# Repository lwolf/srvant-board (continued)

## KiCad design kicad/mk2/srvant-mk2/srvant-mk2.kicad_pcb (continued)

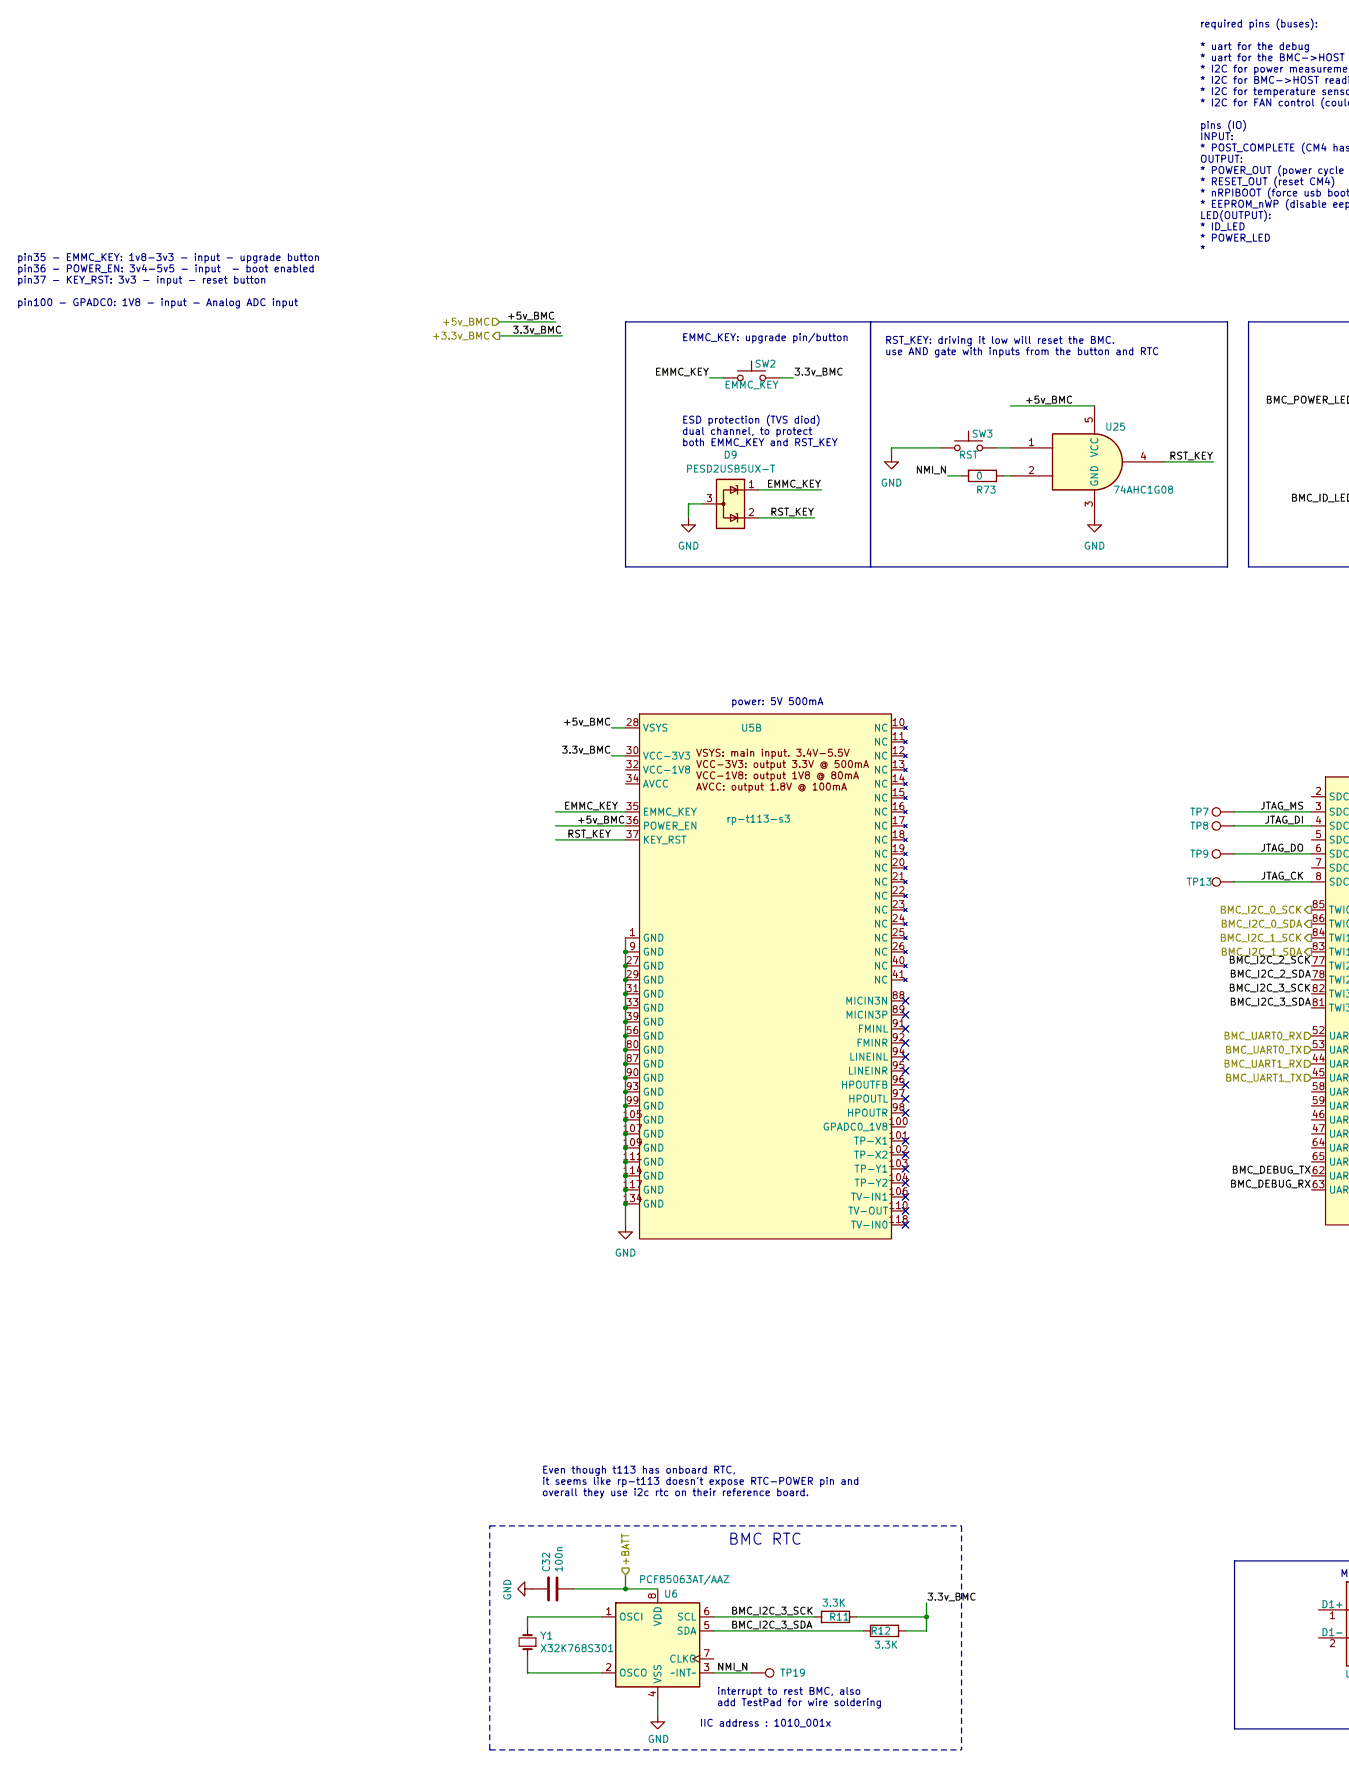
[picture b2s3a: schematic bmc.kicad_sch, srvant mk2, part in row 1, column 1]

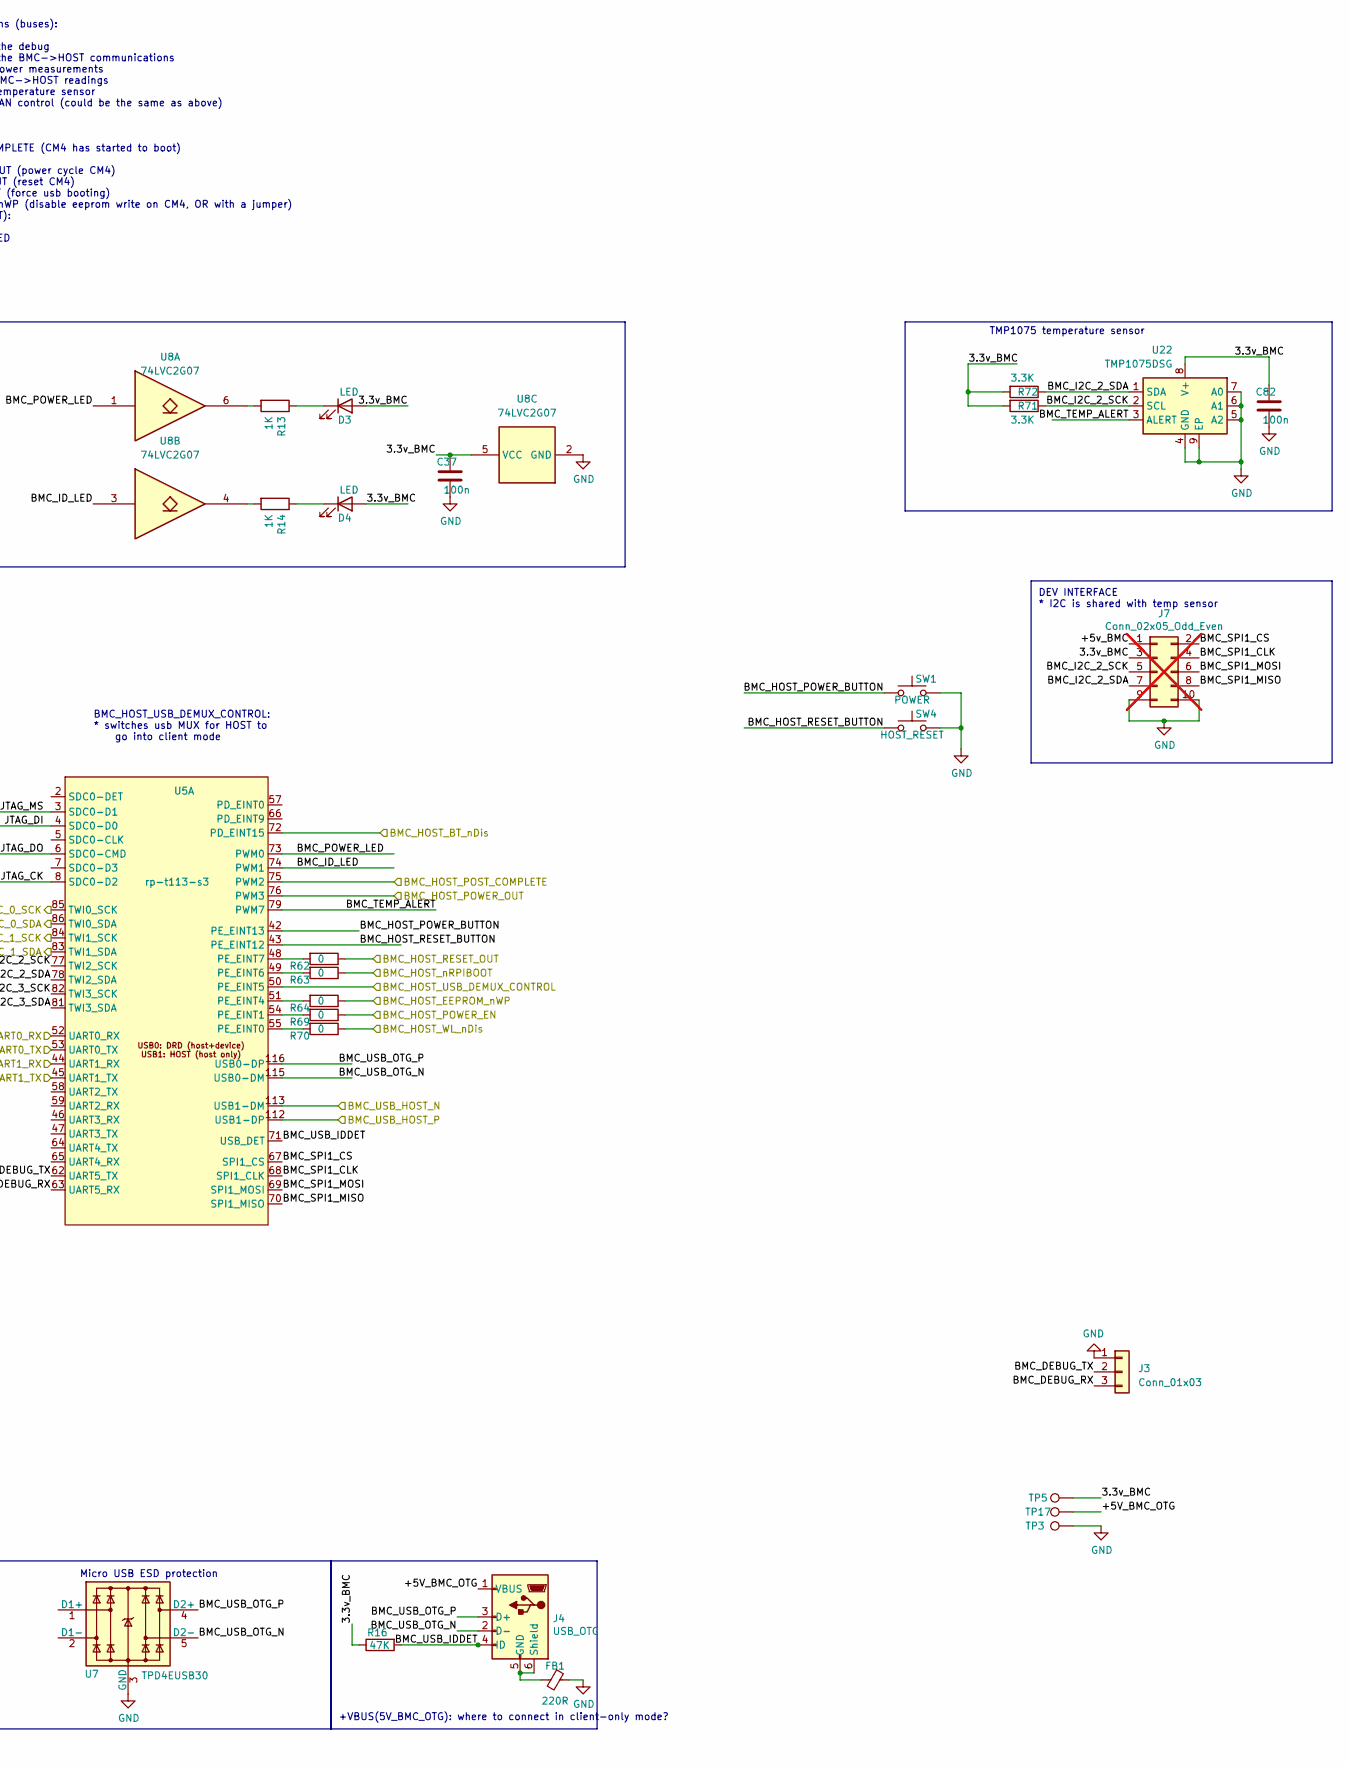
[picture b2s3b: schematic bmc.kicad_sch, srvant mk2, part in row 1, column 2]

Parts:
C32: 100n; C_0402_1005Metric; Part Description 0.1uF 10% 16V Ceramic Capacitor X7R 040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
C37, C82: 100n; C_0402_1005Metric; Part Description 0.1uF 10% 16V Ceramic Capacitor X7R 040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; digikey# EMK105B7104KV-F
D3, D4: LED; LED_0603_1608Metric; Part Description Red 620nm LED Indication - Discrete 2.2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
D9: PESD2USB5UX-T; SOT-23; mouser# 771-PESD2USB5UXT-QR
FB1: 220R; R_0402_1005Metric; mouser# 81-BLM15PX221SH1D
J3: Conn_01x03; PinHeader_1x03_P2.54mm_Vertical
J4: USB_OTG; USB_Micro-B_Amphenol_10103594-0001LF_Horizontal; Part Description USB - micro B USB 2.0 Receptacle Connec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
J7: Conn_02x05_Odd_Even; PinHeader_2x05_P2.54mm_Vertical; Part Description PinHeader_2x05_P2.54mm_Vertical; not fitted
R11, R12, R71, R72: 3.3K; R_0402_1005Metric
R13, R14: 1K; R_0402_1005Metric; Part Description Resistor 1K M1005 1% 63mW
R16: 47K; R_0402_1005Metric; Part Description Resistor 1K M1005 1% 63mW
R62, R63, R64, R69, R70, R73: 0; R_0402_1005Metric
SW1: POWER; button-SW_TL3340AF160QG; farnell# 2787247
SW2: EMMC_KEY; SW4_FSM-5P23_TEC
SW3: RST; SW4_FSM-5P23_TEC
SW4: HOST_RESET; button-SW_TL3340AF160QG; farnell# 2787247
TP3: GND; TestPoint_Pad_D1.0mm
TP5: 3.3v BMC; TestPoint_Pad_D1.0mm
TP7: MS; TestPoint_Pad_D1.0mm
TP8: DI; TestPoint_Pad_D1.0mm
TP9: DO; TestPoint_Pad_D1.0mm
TP13: CK; TestPoint_Pad_D1.0mm
TP17: 5v OTG; TestPoint_Pad_D1.0mm
TP19: NMI_N; TestPoint_Pad_D1.0mm
U5: rp-t113-s3
U6: PCF85063AT/AAZ; SOIC-8_3.9x4.9mm_P1.27mm; Part Description Real Time Clock (RTC) IC Clock/Calendar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
U7: TPD4EUSB30; USON-10_2.5x1.0mm_P0.5mm; Part Description Quad TVS diode for high speed signals (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
U8: 74LVC2G07; SOT-23-6; mouser# 595-SN74LVC2G07DBVR
U22: TMP1075DSG; WSON-8-1EP_2x2mm_P0.5mm_EP0.9x1.6mm_ThermalVias; mouser# 595-TMP1075DSGR
U25: 74AHC1G08; SOT-23-5; mouser# 595-SN74AHC1G08DBVR
Y1: X32K768S301; Crystal_SMD_2012-2Pin_2.0x1.2mm; Part Description Crystal 32.768KHz 7pF 20pmm; digikey# 535-14101-2-ND

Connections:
/BMC ethernet/PHY_MDIO: U5.118 (RMII-MDIO); also elsewhere on the board
/bmc/+5v_BMC: J7.1, U5.28 (VSYS), U5.36 (POWER_EN), U25.5 (VCC); also elsewhere on the board
/bmc/BMC_DEBUG_RX: J3.3, U5.63 (UART5_RX)
/bmc/BMC_DEBUG_TX: J3.2, U5.62 (UART5_TX)
/bmc/BMC_HOST_BT_nDis: U5.72 (PD_EINT15); also elsewhere on the board
/bmc/BMC_HOST_EEPROM_nWP: R64.1; also elsewhere on the board
/bmc/BMC_HOST_POST_COMPLETE: R62.1, U5.75 (PWM2); also elsewhere on the board
/bmc/BMC_HOST_POWER_BUTTON: SW1.1, U5.42 (PE_EINT13)
/bmc/BMC_HOST_POWER_OUT: U5.76 (PWM3); also elsewhere on the board
/bmc/BMC_HOST_RESET_BUTTON: SW4.1, U5.43 (PE_EINT12)
/bmc/BMC_HOST_WL_nDis: R70.1; also elsewhere on the board
/bmc/BMC_HOST_nRPIBOOT: R63.1; also elsewhere on the board
/bmc/BMC_I2C_2_SCK: J7.5, R71.1, U5.77 (TWI2_SCK), U22.2 (SCL)
/bmc/BMC_I2C_2_SDA: J7.7, R72.1, U5.78 (TWI2_SDA), U22.1 (SDA)
/bmc/BMC_I2C_3_SCK: R11.2, U5.82 (TWI3_SCK), U6.6 (SCL)
/bmc/BMC_I2C_3_SDA: R12.1, U5.81 (TWI3_SDA), U6.5 (SDA)
/bmc/BMC_ID_LED: U5.74 (PWM1), U8.3
/bmc/BMC_POWER_LED: U5.73 (PWM0), U8.1
/bmc/BMC_SPI1_CLK: J7.4, U5.68 (SPI1_CLK)
/bmc/BMC_SPI1_CS: J7.2, U5.67 (SPI1_CS)
/bmc/BMC_SPI1_MISO: J7.8, U5.70 (SPI1_MISO)
/bmc/BMC_SPI1_MOSI: J7.6, U5.69 (SPI1_MOSI)
/bmc/BMC_TEMP_ALERT: U5.79 (PWM7), U22.3 (ALERT)
/bmc/BMC_UART0_RX: U5.52 (UART0_RX); also elsewhere on the board
/bmc/BMC_UART0_TX: U5.53 (UART0_TX); also elsewhere on the board
/bmc/BMC_UART1_RX: U5.44 (UART1_RX); also elsewhere on the board
/bmc/BMC_UART1_TX: U5.45 (UART1_TX); also elsewhere on the board
/bmc/BMC_USB_HOST_N: U5.113 (USB1-DM); also elsewhere on the board
/bmc/BMC_USB_HOST_P: U5.112 (USB1-DP); also elsewhere on the board
/bmc/BMC_USB_OTG_N: J4.2 (D-), U5.115 (USB0-DM), U7.5 (D2-), U7.6
/bmc/BMC_USB_OTG_P: J4.3 (D+), U5.116 (USB0-DP), U7.4 (D2+), U7.7
/bmc/EMMC_KEY: D9.1 (K), SW2.1, U5.35 (EMMC_KEY)
/bmc/JTAG_CK: TP13.1, U5.8 (SDC0-D2)
/bmc/JTAG_DI: TP8.1, U5.4 (SDC0-D0)
/bmc/JTAG_DO: TP9.1, U5.6 (SDC0-CMD)
/bmc/JTAG_MS: TP7.1, U5.3 (SDC0-D1)
/bmc/NMI_N: R73.2, TP19.1, U6.3 (~INT~)
/bmc/RST_KEY: D9.2 (K), U5.37 (KEY_RST), U25.4
/cm4/+BATT: C32.2, U6.8 (VDD); also elsewhere on the board
/cm4/GPIO10: U5.83 (TWI1_SDA); also elsewhere on the board
/cm4/GPIO11: U5.84 (TWI1_SCK); also elsewhere on the board
/cm4/USBOTG_ID: U5.50 (PE_EINT5); also elsewhere on the board
/power/BMC_HOST_POWER_EN: R69.1; also elsewhere on the board
/power/BMC_I2C_0_SCK: U5.85 (TWI0_SCK); also elsewhere on the board
/power/BMC_I2C_0_SDA: U5.86 (TWI0_SDA); also elsewhere on the board
unnamed: D3.1 (K), R13.1
unnamed: D4.1 (K), R14.1
unnamed: FB1.2, J4.5 (GND), J4.6 (Shield)
unnamed: R13.2, U8.6
unnamed: R14.2, U8.4
unnamed: R73.1, U25.2
unnamed: SW3.2, U25.1
unnamed: R70.2, U5.55 (PE_EINT0)
unnamed: R69.2, U5.54 (PE_EINT1)
unnamed: R64.2, U5.51 (PE_EINT4)
unnamed: R63.2, U5.49 (PE_EINT6)
unnamed: R62.2, U5.48 (PE_EINT7)
unnamed: U6.1 (OSCI), Y1.2
unnamed: U6.2 (OSCO), Y1.1
unnamed: U7.1 (D1+), U7.10
unnamed: U7.2 (D1-), U7.9

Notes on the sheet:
pin35 - EMMC_KEY: 1v8-3v3 - input - upgrade button pin36 - POWER_EN: 3v4-5v5 - input - boot enabled pin37 - KEY_RST: 3v3 - input - reset button pin100 - GPADC0: 1V8 - input - Analog ADC input
interrupt to rest BMC, also add TestPad for wire soldering
IIC address : 1010_001x
EMMC_KEY: upgrade pin/button
Micro USB ESD protection
RST_KEY: driving it low will reset the BMC. use AND gate with inputs from the button and RTC
ESD protection (TVS diod) dual channel, to protect both EMMC_KEY and RST_KEY
required pins (buses): * uart for the debug * uart for the BMC->HOST communications * I2C for power measurements * I2C for BMC->HOST readings * I2C for temperature sensor * I2C for FAN control (could be the same as above) pins (IO) INPUT: * POST_COMPLETE (CM4 has started to boot) OUTPUT: * POWER_OU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
DEV INTERFACE * I2C is shared with temp sensor
Even though t113 has onboard RTC, it seems like rp-t113 doesn't expose RTC-POWER pin and overall they use i2c rtc on their reference board.
power: 5V 500mA
BMC RTC
BMC_HOST_USB_DEMUX_CONTROL: * switches usb MUX for HOST to go into client mode
TMP1075 temperature sensor
+VBUS(5V_BMC_OTG): where to connect in client-only mode?

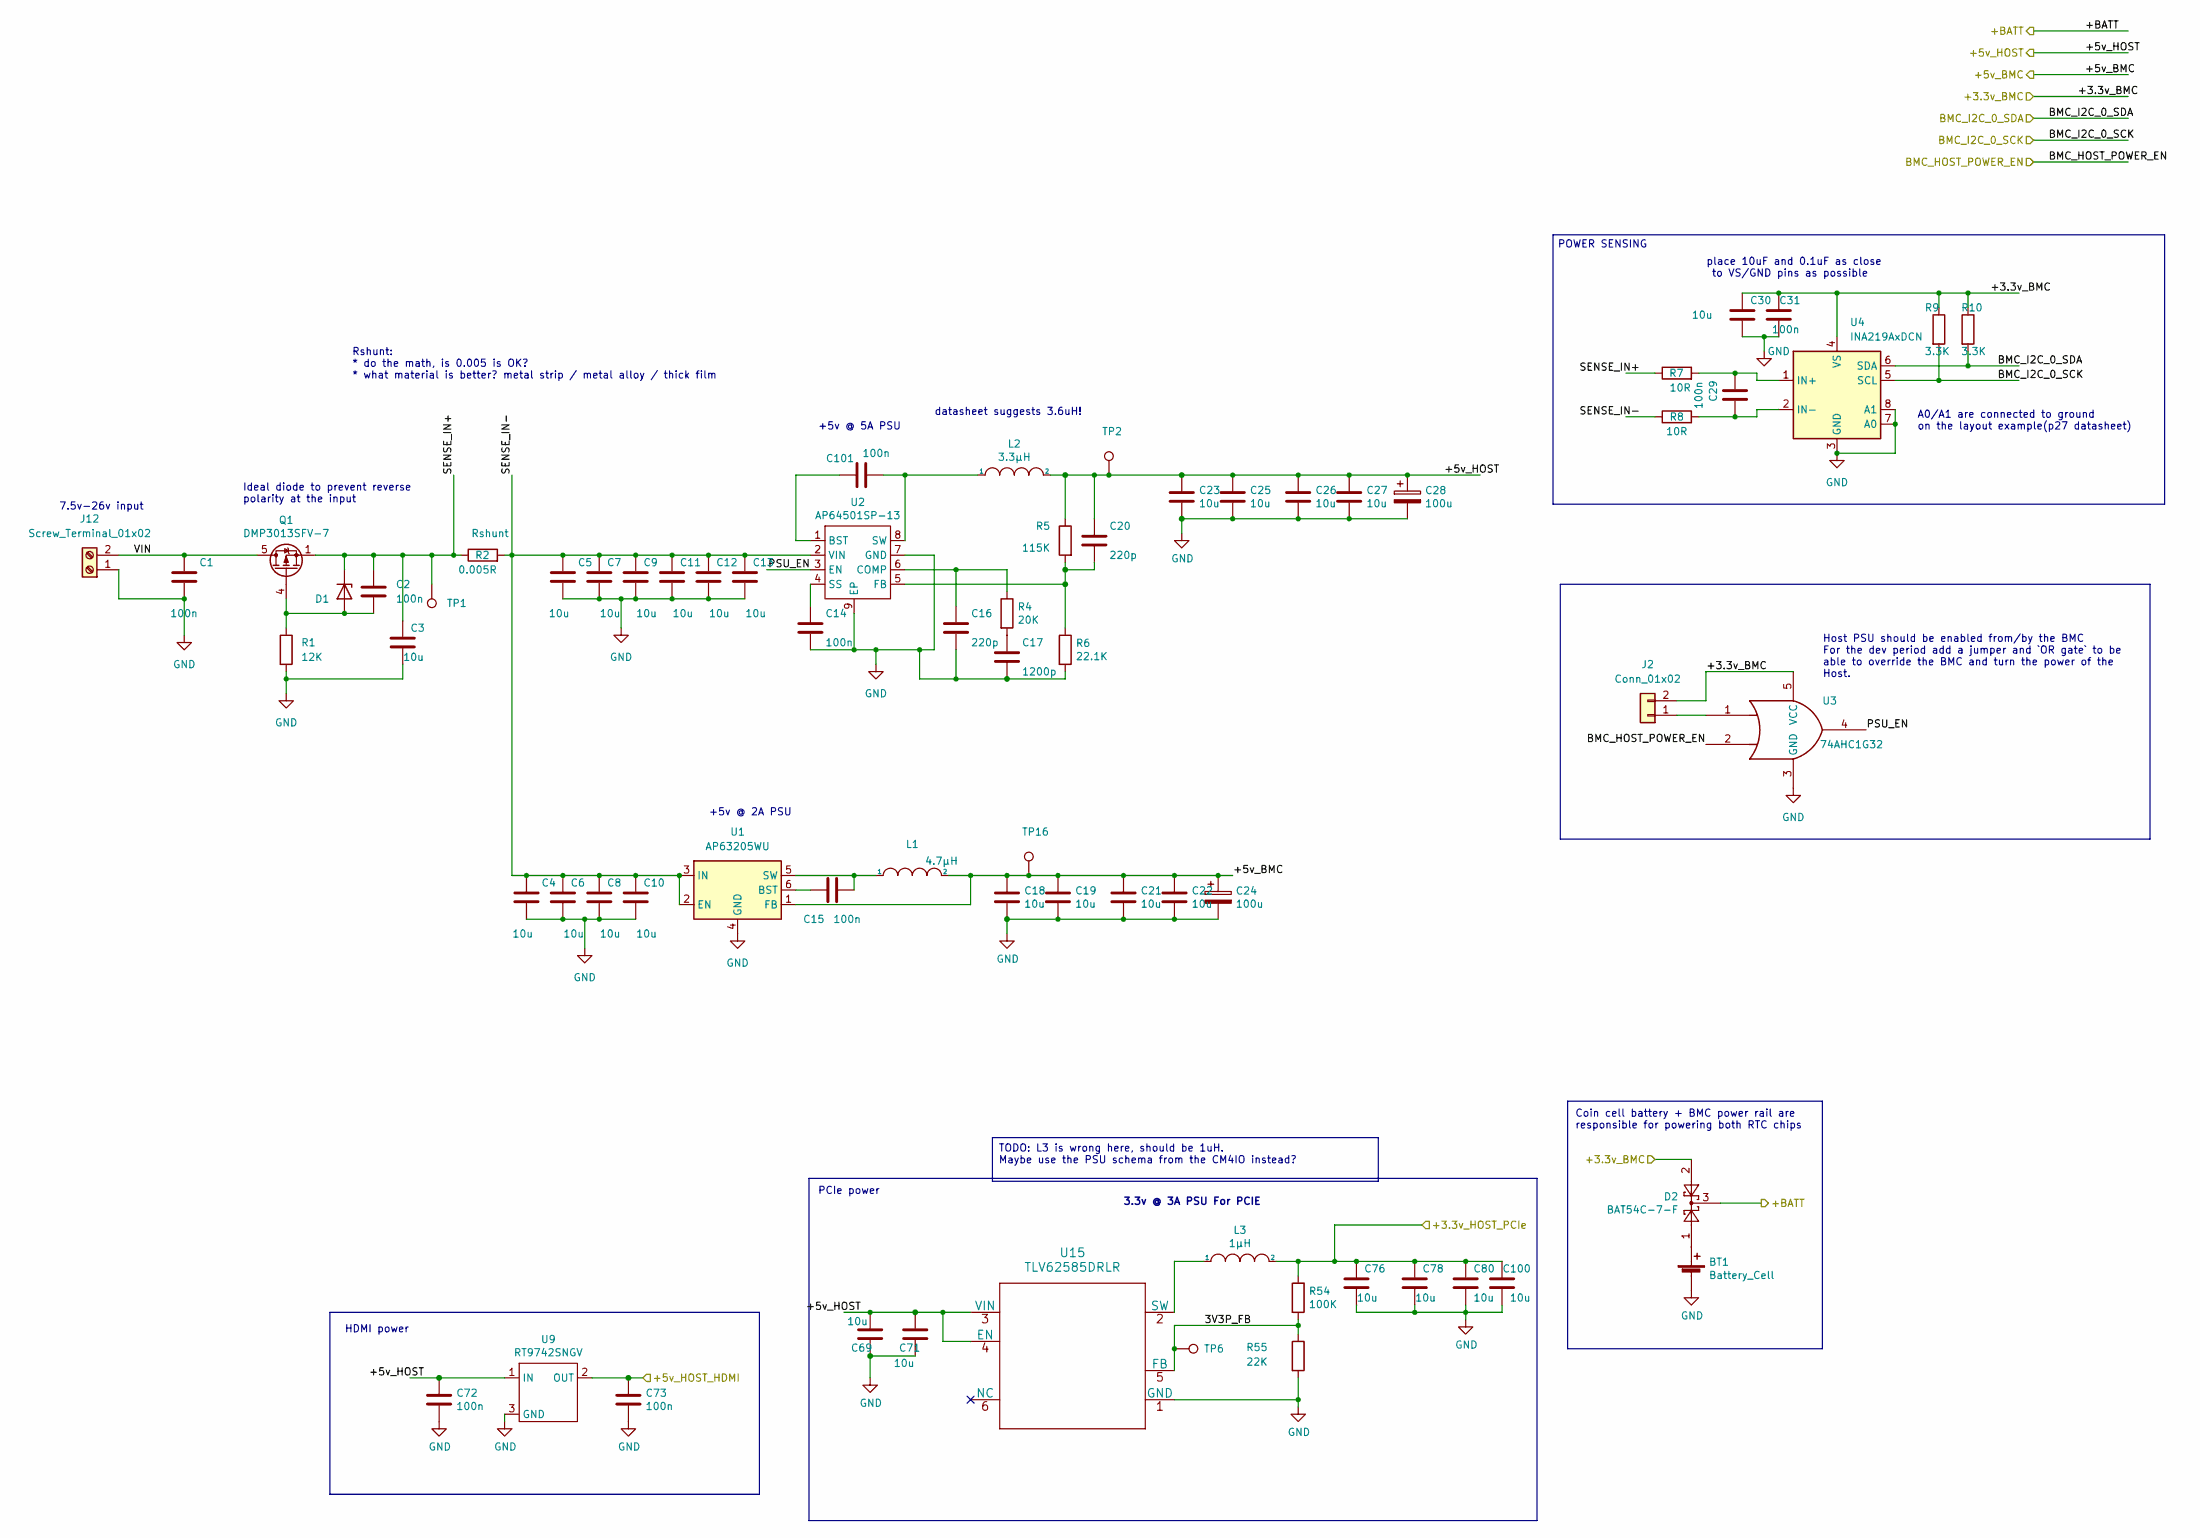
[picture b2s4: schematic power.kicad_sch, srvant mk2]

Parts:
BT1: Battery_Cell; battery-S8411-45R
C1: 100n; C_1206_3216Metric; Part Description 0.1uF 10% 100V Ceramic Capacitor X5R 04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; farnell# 2611907
C2, C31: 100n; C_0402_1005Metric; Part Description 0.1uF 10% 16V Ceramic Capacitor X7R 040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; farnell# 2611911
C3, C4, C5, C6, C7, C8, C9, C10, C11, C12, C13: 10u; C_0805_2012Metric; Part Description 10uF 10% or 20% 35V Ceramic Capacitor X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; digikey# 490-10505-1-ND
C14, C15, C29: 100n; C_0402_1005Metric; Part Description 0.1uF 10% 16V Ceramic Capacitor X7R 040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; digikey# EMK105B7104KV-F
C16, C20: 220p; C_0402_1005Metric; Part Description 220 pF, 50 V, 0402 [1005 Metric], ± 5%,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; farnell# 2666374
C17: 1200p; C_0402_1005Metric; Part Description 1200pF 10% 10V Ceramic Capacitor X5R 04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; digikey# 490-16429-1-ND
C18, C19, C21, C22, C23, C25, C26, C27, C69, C71, C76, C78, C80, C100: 10u; C_0805_2012Metric; Part Description 10uF 10% 10V Ceramic Capacitor X7R 0805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; digikey# 490-14381-1-ND
C24, C28: 100u; CP_EIA-7343-31_Kemet-D; Part Description Capacitor, SP-Cap, 100u, 6.3V, 15mR ESR; mouser# ECASD40J107M015K00
C30: 10u; C_0402_1005Metric; Part Description 10uF 10% or 20% 35V Ceramic Capacitor X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; digikey# 490-10505-1-ND
C72, C73, C101: 100n; C_0402_1005Metric; Part Description 0.1uF 10% 16V Ceramic Capacitor X7R 040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
D1: MMBZ5242BLT3G; SOT-23-3_1P4X3P040_ONS; Part Description Zener Diode 12V 225mW 5% Surface Mount 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; digikey# MMBZ5242BLT3GOSCT-ND
D2: BAT54C-7-F; SOT-23; Part Description Diode Array 1 Pair Common Cathode Schot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
J2: Conn_01x02; PinHeader_1x02_P2.54mm_Vertical
J12: Screw_Terminal_01x02; TerminalBlock_bornier-2_P5.08mm
L1: 4.7µH; L_Bourns-SRN4018; Part Description 4.7µH Semi-Shielded Wirewound Inductor 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; mouser# 652-SRN4018-4R7M
L2: 3.3µH; L_Bourns_SRN6045TA; Part Description 3.3µH Semi-Shielded Wirewound Inductor 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; farnell# 2616889
L3: 1µH; L_Bourns_SRN6045TA; Part Description 1µH Semi-Shielded Wirewound Inductor 8A; farnell# 2616885
Q1: DMP3013SFV-7; Diodes_PowerDI3333-8; Part Description DMP3013SFV-7 - Power MOSFET, P Channel,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; mouser# 621-DMP3013SFV-7
R1: 12K; R_0402_1005Metric; Part Description Resistor 12K M1005 1% 63mW; farnell# 9239367
R2: 0.005R; R_0805_2012Metric; Part Description Rshunt; farnell# 2729138
R4: 20K; R_0402_1005Metric; Part Description Resistor 20K M1005 1% 63mW; farnell# 2331485
R5: 115K; R_0402_1005Metric
R6: 22.1K; R_0402_1005Metric
R7, R8: 10R; R_0402_1005Metric; Part Description Resistor 10R M1005 1% 63mW; farnell# 9238999
R9, R10: 3.3K; R_0402_1005Metric
R54: 100K; R_0402_1005Metric; Part Description Resistor 100K M1005 1% 63mW
R55: 22K; R_0402_1005Metric; Part Description Resistor 22K M1005 1% 63mW; farnell# 9239430
TP1, TP6: VIN; TestPoint_Pad_D1.0mm
TP2: +5v HOST; TestPoint_Pad_2.0x2.0mm
TP16: +5v BMC; TestPoint_Pad_D1.0mm
U1: AP63205WU; TSOT-23-6; mouser# 621-AP63205WU-7
U2: AP64501SP-13; SOIC-8-1EP_3.9x4.9mm_P1.27mm_EP2.95x4.9mm_Mask2.71x3.4mm_Th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; Part Description Buck Switching Regulator IC Positive Ad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; digikey# 31-AP64501SP-13CT-ND
U3: 74AHC1G32; SOT-23-5; mouser# 595-SN74AHC1G32DBVR
U4: INA219AxDCN; SOT-23-8; mouser# 595-INA219AIDCNR
U9: RT9742SNGV; SOT-23; Part Description Power Switch/Driver 1:1 N-Channel 500mA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; mouser# 835-RT9742SNGV
U15: TLV62585DRLR; DRL0006A; mouser# 595-TLV62585DRLR

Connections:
/bmc/+5v_BMC: C18.1, C19.1, C21.1, C22.1, C24.1, L1.2, TP16.1, U1.1 (FB); also elsewhere on the board
/cm4/+3.3v_HOST_PCIe: C76.1, C78.1, C80.1, C100.1, L3.2, R54.1; also elsewhere on the board
/cm4/+5v_HOST: C20.1, C23.1, C25.1, C26.1, C27.1, C28.1, C69.1, C71.1, C72.1, L2.2, R5.1, TP2.1, U9.1 (IN), U15.3 (VIN), U15.4 (EN); also elsewhere on the board
/cm4/+5v_HOST_HDMI: C73.1, U9.2 (OUT); also elsewhere on the board
/cm4/+BATT: D2.3; also elsewhere on the board
/power/3V3P_FB: R54.2, R55.1, TP6.1, U15.5 (FB)
/power/BMC_HOST_POWER_EN: U3.2; also elsewhere on the board
/power/BMC_I2C_0_SCK: R9.2, U4.5 (SCL); also elsewhere on the board
/power/BMC_I2C_0_SDA: R10.2, U4.6 (SDA); also elsewhere on the board
/power/PSU_EN: U2.3 (EN), U3.4
/power/SENSE_IN+: C2.1, C3.1, D1.1 (K), Q1.1 (S), Q1.2 (S), Q1.3 (S), R2.1, R7.1, TP1.1
/power/SENSE_IN-: C4.1, C5.1, C6.1, C7.1, C8.1, C9.1, C10.1, C11.1, C12.1, C13.1, R2.2, R8.1, U1.2 (EN), U1.3 (IN), U2.2 (VIN)
/power/VIN: C1.1, J12.2, Q1.5 (D)
unnamed: BT1.1 (+), D2.1
unnamed: C17.1, R4.2
unnamed: C2.2, D1.2 (A), Q1.4 (G), R1.1
unnamed: J2.1, U3.1
unnamed: C15.1, U1.6 (BST)
unnamed: C15.2, L1.1, U1.5 (SW)
unnamed: C101.1, U2.1 (BST)
unnamed: C16.1, R4.1, U2.6 (COMP)
unnamed: C20.2, R5.2, R6.1, U2.5 (FB)
unnamed: C14.1, U2.4 (SS)
unnamed: C101.2, L2.1, U2.8 (SW)
unnamed: C29.1, R7.2, U4.1 (IN+)
unnamed: C29.2, R8.2, U4.2 (IN-)
unnamed: L3.1, U15.2 (SW)

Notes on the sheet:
TODO: L3 is wrong here, should be 1uH. Maybe use the PSU schema from the CM4IO instead?
A0/A1 are connected to ground on the layout example(p27 datasheet)
Host PSU should be enabled from/by the BMC For the dev period add a jumper and `OR gate` to be able to override the BMC and turn the power of the Host.
datasheet suggests 3.6uH!
3.3v @ 3A PSU For PCIE
Ideal diode to prevent reverse polarity at the input
7.5v-26v input
place 10uF and 0.1uF as close to VS/GND pins as possible
HDMI power
+5v @ 5A PSU
Rshunt: * do the math, is 0.005 is OK? * what material is better? metal strip / metal alloy / thick film
POWER SENSING
PCIe power
Coin cell battery + BMC power rail are responsible for powering both RTC chips
+5v @ 2A PSU

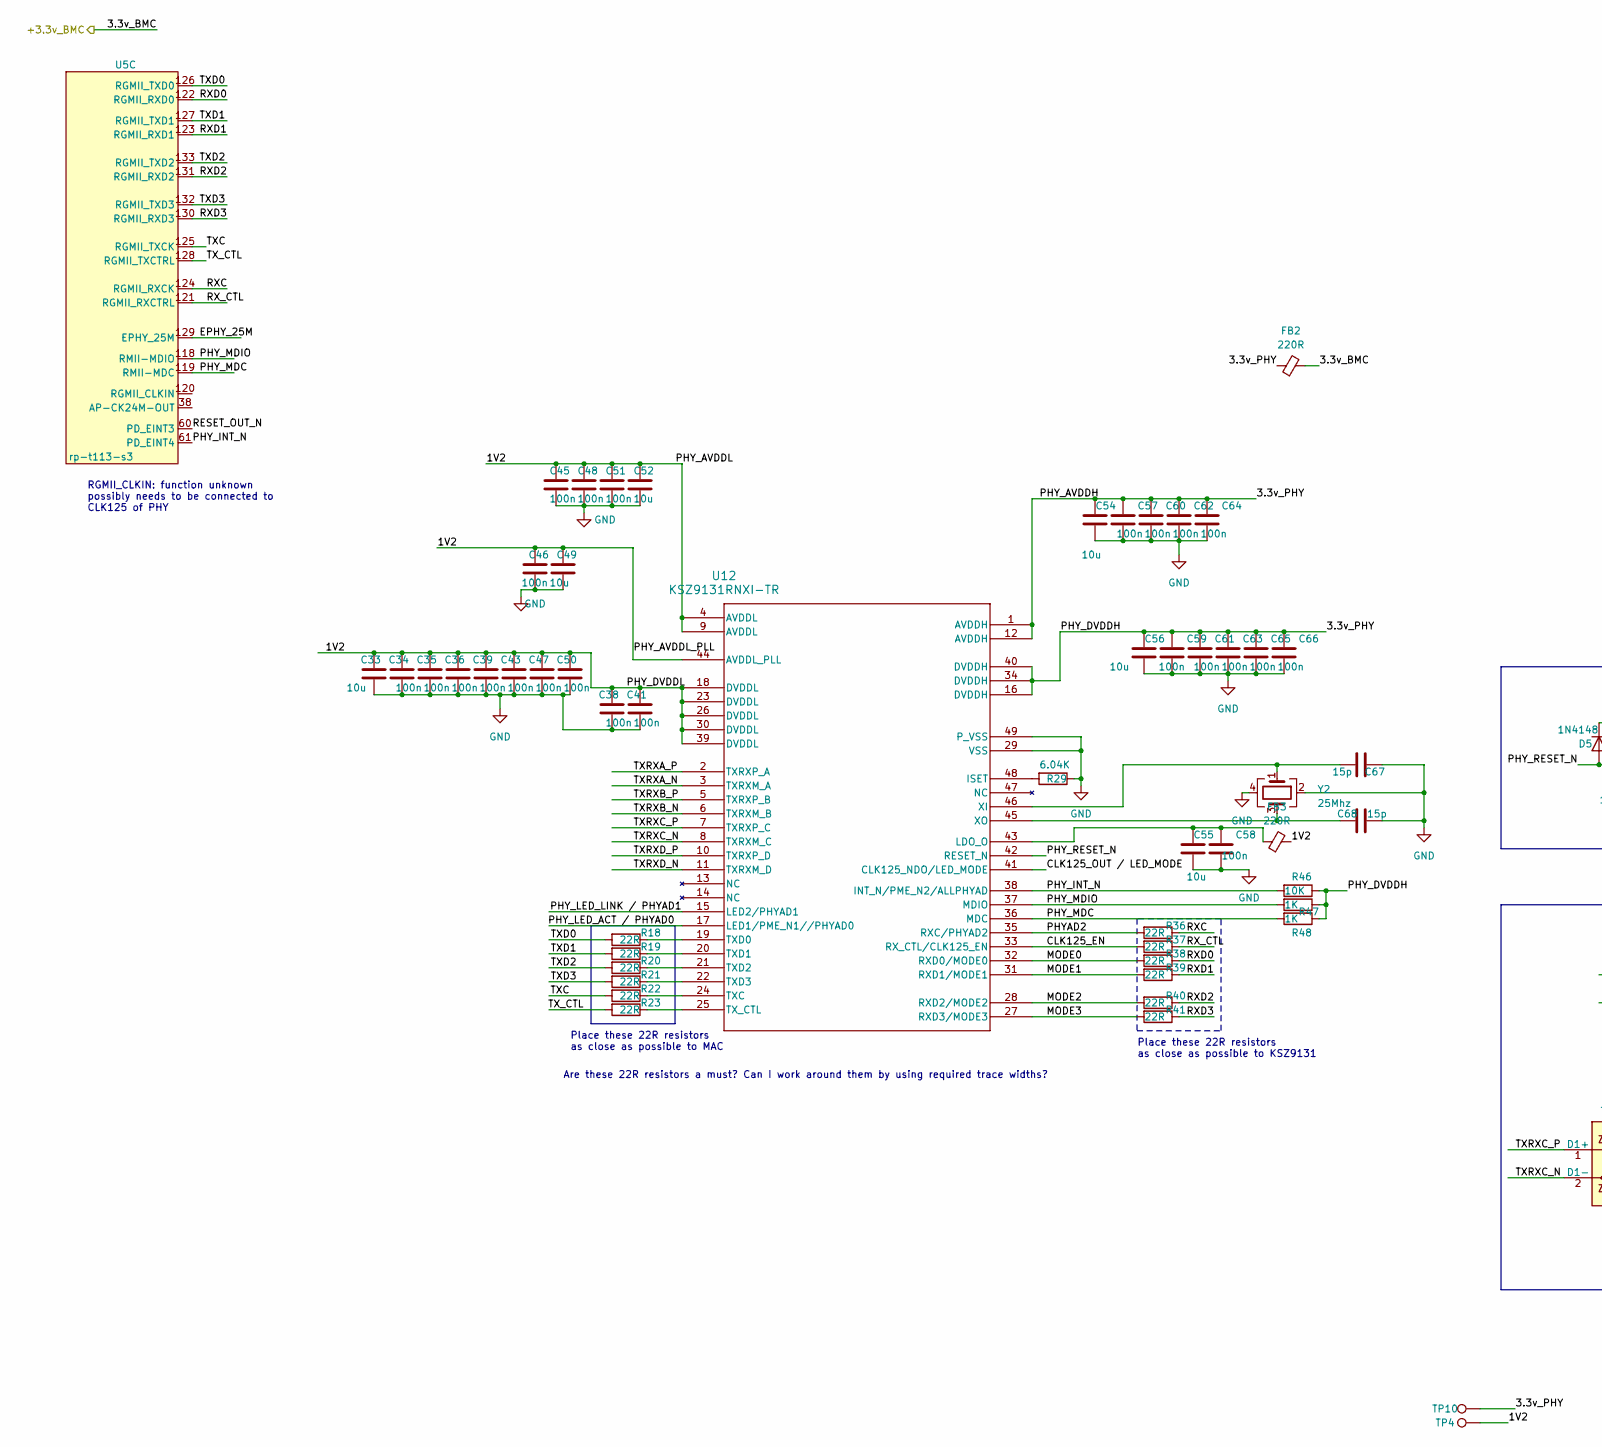
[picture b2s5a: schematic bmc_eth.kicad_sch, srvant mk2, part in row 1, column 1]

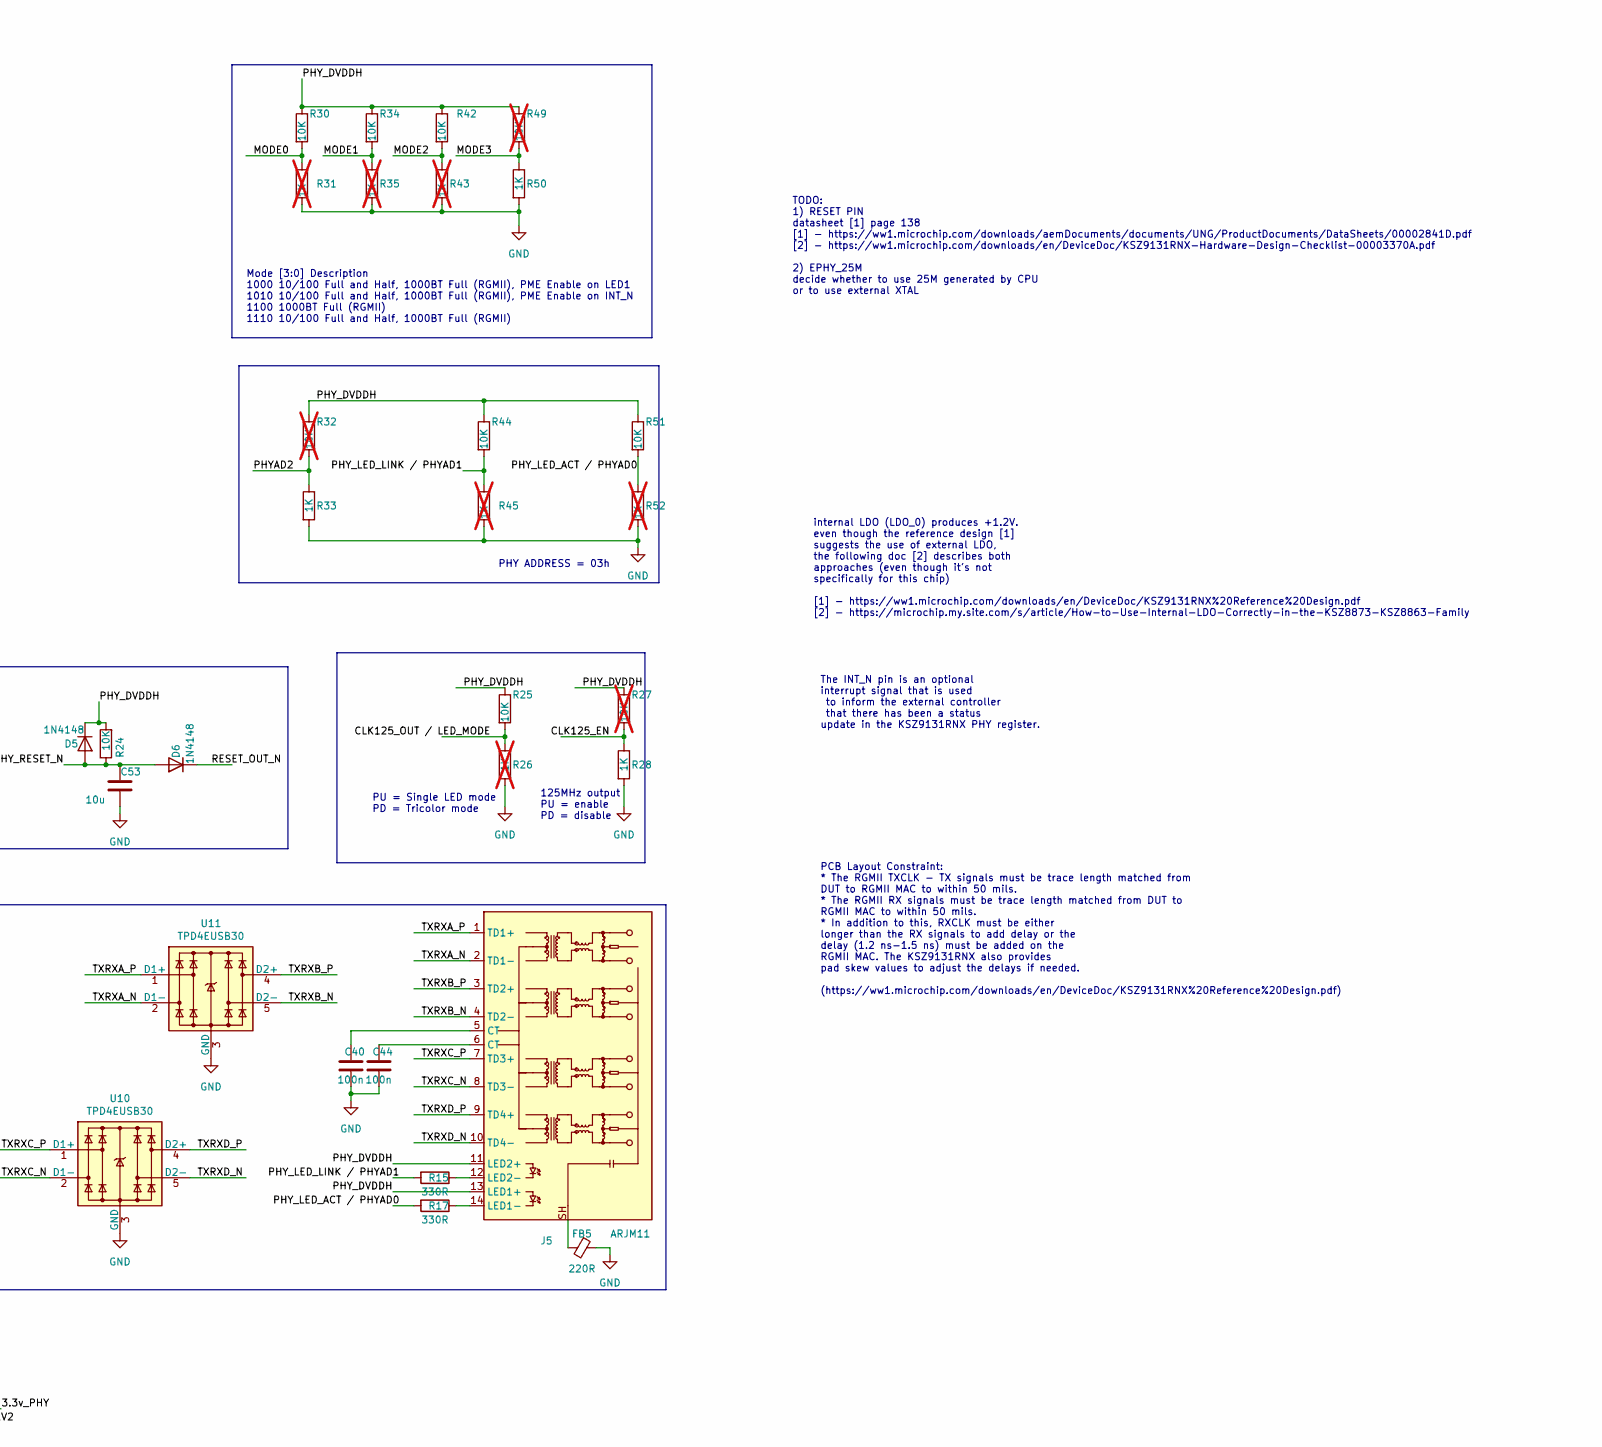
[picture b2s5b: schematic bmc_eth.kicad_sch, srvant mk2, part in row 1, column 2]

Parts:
C33, C49, C52, C53, C54, C55, C56: 10u; C_0402_1005Metric; Part Description 10uF 10% or 20% 35V Ceramic Capacitor X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; digikey# 490-10505-1-ND
C34, C35, C36, C38, C39, C40, C41, C43, C44, C45, C46, C47, C48, C50, C51, C57, C58, C59, C60, C61, C62, C63, C64, C65, C66: 100n; C_0402_1005Metric; Part Description 0.1uF 10% 16V Ceramic Capacitor X7R 040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; digikey# EMK105B7104KV-F
C67, C68: 15p; C_0402_1005Metric; Part Description SMD Multilayer Ceramic Capacitor, 15 pF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; farnell# 2627389
D5, D6: 1N4148; D_SOD-523; mouser# 621-1N4148WT
FB2, FB3, FB5: 220R; R_0402_1005Metric; mouser# 81-BLM15PX221SH1D
J5: ARJM11; RJ45_Wuerth_7499111446_Horizontal
R15, R17: 330R; R_0402_1005Metric
R18, R19, R20, R21, R22, R23, R36, R37, R38, R39, R40, R41: 22R; R_0402_1005Metric
R24, R25, R30, R34, R42, R44, R46, R51: 10K; R_0402_1005Metric
R26, R31, R35, R43, R45, R52: 1K; R_0402_1005Metric; Part Description Resistor 1K M1005 1% 63mW; not fitted
R27, R32, R49: 10K; R_0402_1005Metric; not fitted
R28, R33, R47, R48, R50: 1K; R_0402_1005Metric; Part Description Resistor 1K M1005 1% 63mW
R29: 6.04K; R_0402_1005Metric; farnell# 3495661
TP4: 1v2; TestPoint_Pad_D1.0mm
TP10: PHY_AVDDH(3.3v); TestPoint_Pad_D1.0mm
U5: rp-t113-s3
U10, U11: TPD4EUSB30; USON-10_2.5x1.0mm_P0.5mm; Part Description Quad TVS diode for high speed signals (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
U12: KSZ9131RNXI-TR; QFN48_NX_MCH; mouser# 579-KSZ9131RNXC-TR; digikey# KSZ9131RNXC-TR
Y2: 25Mhz; Crystal_SMD_FOX_FQ7050-4Pin_7.0x5.0mm; farnell# 2854241

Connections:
/BMC ethernet/1V2: C33.1, C34.1, C35.1, C36.1, C38.1, C39.1, C41.1, C43.1, C45.1, C46.1, C47.1, C48.1, C49.1, C50.1, C51.1, C52.1, FB3.2, TP4.1, U12.4 (AVDDL), U12.9 (AVDDL), U12.18 (DVDDL), U12.23 (DVDDL), U12.26 (DVDDL), U12.30 (DVDDL), U12.39 (DVDDL), U12.44 (AVDDL_PLL)
/BMC ethernet/EPHY_25M: U5.129 (EPHY_25M)
/BMC ethernet/PHY_INT_N: R46.2, U5.61 (PD_EINT4), U12.38 (INT_N/PME_N2/ALLPHYAD)
/BMC ethernet/PHY_MDC: R48.2, U5.119 (RMII-MDC), U12.36 (MDC)
/BMC ethernet/PHY_MDIO: R47.2, U5.118 (RMII-MDIO), U12.37 (MDIO)
/BMC ethernet/PHY_RESET_N: C53.1, D5.2 (A), D6.2 (A), R24.1, U12.42 (RESET_N)
/BMC ethernet/RESET_OUT_N: D6.1 (K), U5.60 (PD_EINT3)
/BMC ethernet/RXC: R36.1, U5.124 (RGMII_RXCK)
/BMC ethernet/RXD0: R38.1, U5.122 (RGMII_RXD0)
/BMC ethernet/RXD1: R39.1, U5.123 (RGMII_RXD1)
/BMC ethernet/RXD2: R40.1, U5.131 (RGMII_RXD2)
/BMC ethernet/RXD3: R41.1, U5.130 (RGMII_RXD3)
/BMC ethernet/RX_CTL: R37.1, U5.121 (RGMII_RXCTRL)
/BMC ethernet/TXC: R22.2, U5.125 (RGMII_TXCK)
/BMC ethernet/TXD0: R18.2, U5.126 (RGMII_TXD0)
/BMC ethernet/TXD1: R19.2, U5.127 (RGMII_TXD1)
/BMC ethernet/TXD2: R20.2, U5.133 (RGMII_TXD2)
/BMC ethernet/TXD3: R21.2, U5.132 (RGMII_TXD3)
/BMC ethernet/TXRXA_N: J5.2 (TD1-), U11.2 (D1-), U11.9, U12.3 (TXRXM_A)
/BMC ethernet/TXRXA_P: J5.1 (TD1+), U11.1 (D1+), U11.10, U12.2 (TXRXP_A)
/BMC ethernet/TXRXB_N: J5.4 (TD2-), U11.5 (D2-), U11.6, U12.6 (TXRXM_B)
/BMC ethernet/TXRXB_P: J5.3 (TD2+), U11.4 (D2+), U11.7, U12.5 (TXRXP_B)
/BMC ethernet/TXRXC_N: J5.8 (TD3-), U10.2 (D1-), U10.9, U12.8 (TXRXM_C)
/BMC ethernet/TXRXC_P: J5.7 (TD3+), U10.1 (D1+), U10.10, U12.7 (TXRXP_C)
/BMC ethernet/TXRXD_N: J5.10 (TD4-), U10.5 (D2-), U10.6, U12.11 (TXRXM_D)
/BMC ethernet/TXRXD_P: J5.9 (TD4+), U10.4 (D2+), U10.7, U12.10 (TXRXP_D)
/BMC ethernet/TX_CTL: R23.2, U5.128 (RGMII_TXCTRL)
unnamed: C40.1, J5.5 (CT)
unnamed: C44.1, J5.6 (CT)
unnamed: FB5.2, J5.SH
unnamed: J5.14 (LED1-), R17.1
unnamed: J5.12 (LED2-), R15.1
unnamed: R29.2, U12.48 (ISET)
unnamed: C55.1, C58.1, FB3.1, U12.43 (LDO_O)
unnamed: R22.1, U12.24 (TXC)
unnamed: R18.1, U12.19 (TXD0)
unnamed: R19.1, U12.20 (TXD1)
unnamed: R20.1, U12.21 (TXD2)
unnamed: R21.1, U12.22 (TXD3)
unnamed: R23.1, U12.25 (TX_CTL)
unnamed: C67.2, U12.46 (XI), Y2.1
unnamed: C68.1, U12.45 (XO), Y2.3

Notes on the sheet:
Place these 22R resistors as close as possible to MAC
PCB Layout Constraint: * The RGMII TXCLK - TX signals must be trace length matched from DUT to RGMII MAC to within 50 mils. * The RGMII RX signals must be trace length matched from DUT to RGMII MAC to within 50 mils. * In addition to this, RXCLK must be either longer than the RX signals to add dela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
Place these 22R resistors as close as possible to KSZ9131
PHY ADDRESS = 03h
PU = Single LED mode PD = Tricolor mode
RGMII_CLKIN: function unknown possibly needs to be connected to CLK125 of PHY
Are these 22R resistors a must? Can I work around them by using required trace widths?
TODO: 1) RESET PIN datasheet [1] page 138 [1] - https://ww1.microchip.com/downloads/aemDocuments/documents/UNG/ProductDocuments/DataSheets/00002841D.pdf [2] - https://ww1.microchip.com/downloads/en/DeviceDoc/KSZ9131RNX-Hardware-Design-Checklist-00003370A.pdf 2) EPHY_25M decide whether to use 25M ge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
125MHz output PU = enable PD = disable
The INT_N pin is an optional interrupt signal that is used to inform the external controller that there has been a status update in the KSZ9131RNX PHY register.
internal LDO (LDO_0) produces +1.2V. even though the reference design [1] suggests the use of external LDO, the following doc [2] describes both approaches (even though it's not specifically for this chip) [1] - https://ww1.microchip.com/downloads/en/DeviceDoc/KSZ9131RNX%20Reference%20Design.pdf [2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
Mode [3:0] Description 1000 10/100 Full and Half, 1000BT Full (RGMII), PME Enable on LED1 1010 10/100 Full and Half, 1000BT Full (RGMII), PME Enable on INT_N 1100 1000BT Full (RGMII) 1110 10/100 Full and Half, 1000BT Full (RGMII)

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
